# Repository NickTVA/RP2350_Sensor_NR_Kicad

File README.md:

# RP2350_Sensor_NR_Kicad

This repository contains the hardware for a NewRelic IoT demo deivce.  The software is avaialble at this [repository](https://github.com/NickTVA/RP2350_Sensor_NR)

Further documentation and a BOM are upcoming.  The PCB is designed in KiCad and there is a simple 3d printable case designed in OpenSCAD.

The zip of the Gerbers can be used for PCB creation.

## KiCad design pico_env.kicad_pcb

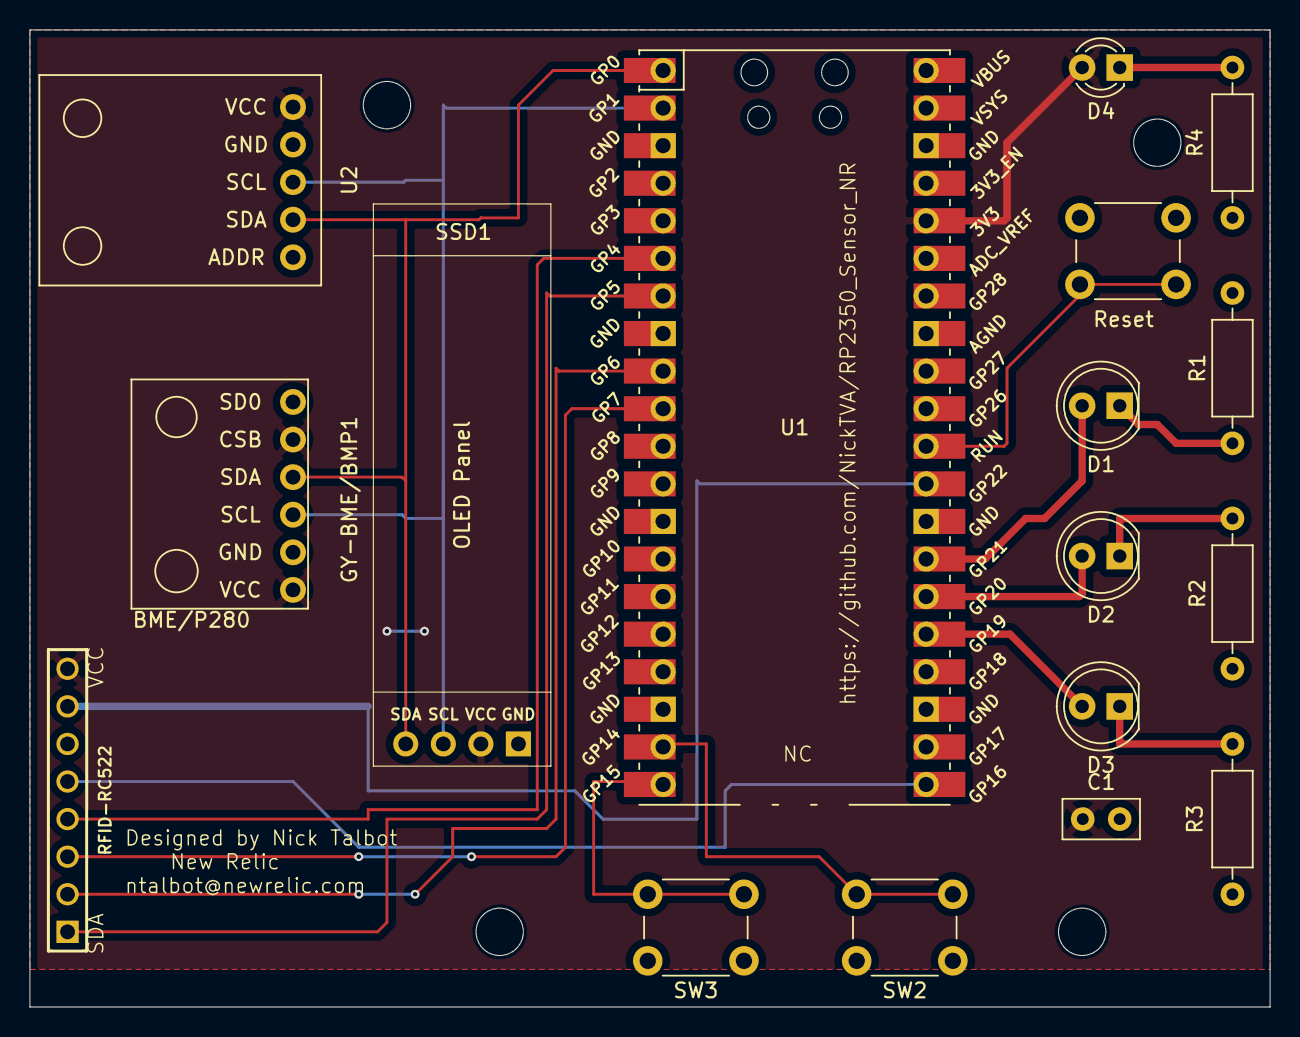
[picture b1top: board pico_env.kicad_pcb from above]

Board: 2 copper layers, 83.8 x 66.0 mm, 17 parts (0 on the bottom side), 20 nets.

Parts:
C1: C; C_Disc_D5.0mm_W2.5mm_P2.50mm
D1: G-LED; LED_D5.0mm
D2: Y-LED; LED_D5.0mm
D3: R-LED; LED_D5.0mm
D4: PWR_LED; LED_D3.0mm
GY-BME/BMP1: module_bme280
R1, R2, R3, R4: R; R_Axial_DIN0207_L6.3mm_D2.5mm_P10.16mm_Horizontal
RFID-RC522: RFID-RC522
Reset: SW_Push; SW_PUSH_6mm
SSD1: SSD1306-0.91-OLED-4pin-128x32
SW2, SW3: SW_Push; SW_PUSH_6mm
U1: Pico; RPi_Pico_SMD_TH
U2: module_bh1750

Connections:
+3.3V: C1.1, D4.2 (A), GY-BME/BMP1.1 (Vin3.3), GY-BME/BMP1.5 (CSB), RFID-RC522.8 (3V3), SSD1.3 (VCC), U1.36 (3V3), U2.5 (VCC)
/MISO: RFID-RC522.4 (MISO), U1.6 (GPIO4)
/MOSI: RFID-RC522.3 (MOSI), U1.10 (GPIO7)
/RFID_IRQ: RFID-RC522.5 (IRQ), U1.21 (GPIO16)
/RFID_RST: RFID-RC522.7 (RST), U1.29 (GPIO22)
/RFID_SCK: RFID-RC522.2 (SCK), U1.9 (GPIO6)
/RFID_SDA: RFID-RC522.1 (SDA), U1.7 (GPIO5)
/SCL: GY-BME/BMP1.3 (SCL), SSD1.2 (SCL), U1.2 (GPIO1), U2.3 (SCL)
/SDA: GY-BME/BMP1.4 (SDA), SSD1.1 (SDA), U1.1 (GPIO0), U2.2 (SDA)
GND: C1.2, GY-BME/BMP1.2 (GND), GY-BME/BMP1.6 (SDO), R1.2, R2.1, R3.2, R4.2, RFID-RC522.6 (GND), Reset.2, SSD1.4 (GND), SW2.1, SW3.1, U1.3 (GND), U1.8 (GND), U1.18 (GND), U1.28 (GND), U1.38 (GND), U2.4 (GND)
unnamed: D1.2 (A), U1.27 (GPIO21)
unnamed: D1.1 (K), R1.1
unnamed: D2.2 (A), U1.26 (GPIO20)
unnamed: D2.1 (K), R2.2
unnamed: D3.2 (A), U1.25 (GPIO19)
unnamed: D3.1 (K), R3.1
unnamed: D4.1 (K), R4.1
unnamed: SW2.2, U1.19 (GPIO14)
unnamed: SW3.2, U1.20 (GPIO15)
unnamed: Reset.1, U1.30 (RUN)

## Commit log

2025-03-14 Added 3d print files
2025-03-19 Fixed bottom_case stl uplaod
2025-03-30 Added headers for RFID
2025-03-31 Moved mounting hole
